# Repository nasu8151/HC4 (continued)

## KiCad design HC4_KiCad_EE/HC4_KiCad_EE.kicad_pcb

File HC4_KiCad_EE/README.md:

Schematics and board of HC4<sub>E</sub> (E means "for Education").

BOM:
[Bill of materials](https://github.com/nasu8151/HC4/blob/main/HC4_KiCad/BOM_HC4.md)

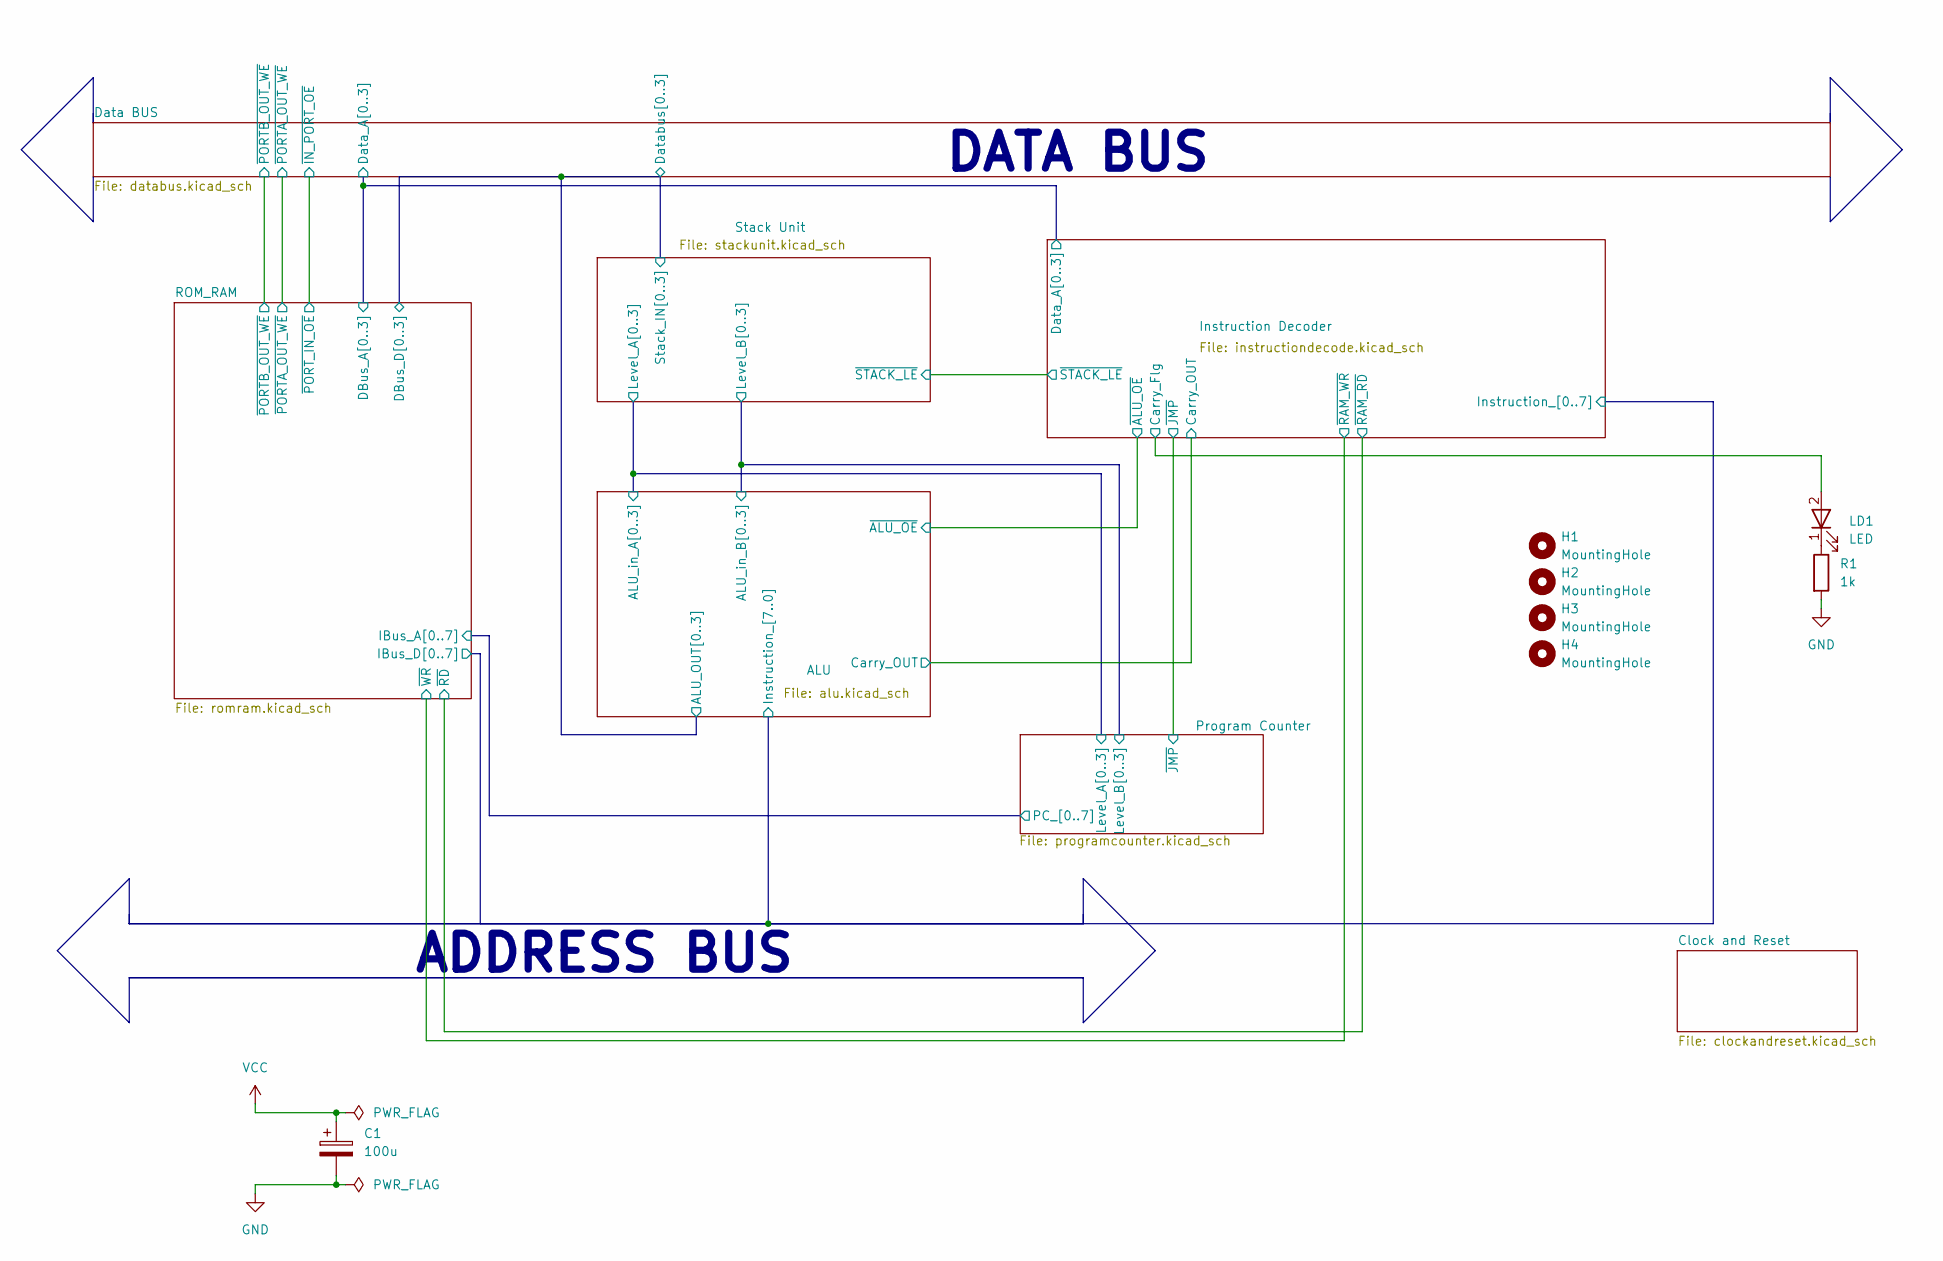
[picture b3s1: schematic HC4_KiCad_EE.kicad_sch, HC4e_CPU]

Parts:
C1: 100u; CP_Radial_D5.0mm_P2.50mm
H1, H2, H3, H4: MountingHole; MountingHole_3.2mm_M3
LD1: LED; LED_Rectangular_W5.0mm_H2.0mm
R1: 1k; R_0603_1608Metric; LCSC PN C21190

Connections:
/Instruction Decoder/Carry_Flg: LD1.2; also elsewhere on the board
GND: C1.2, R1.2; also elsewhere on the board
unnamed: LD1.1 (K_1), R1.1
VCC: C1.1; also elsewhere on the board

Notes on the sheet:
ADDRESS BUS
DATA BUS

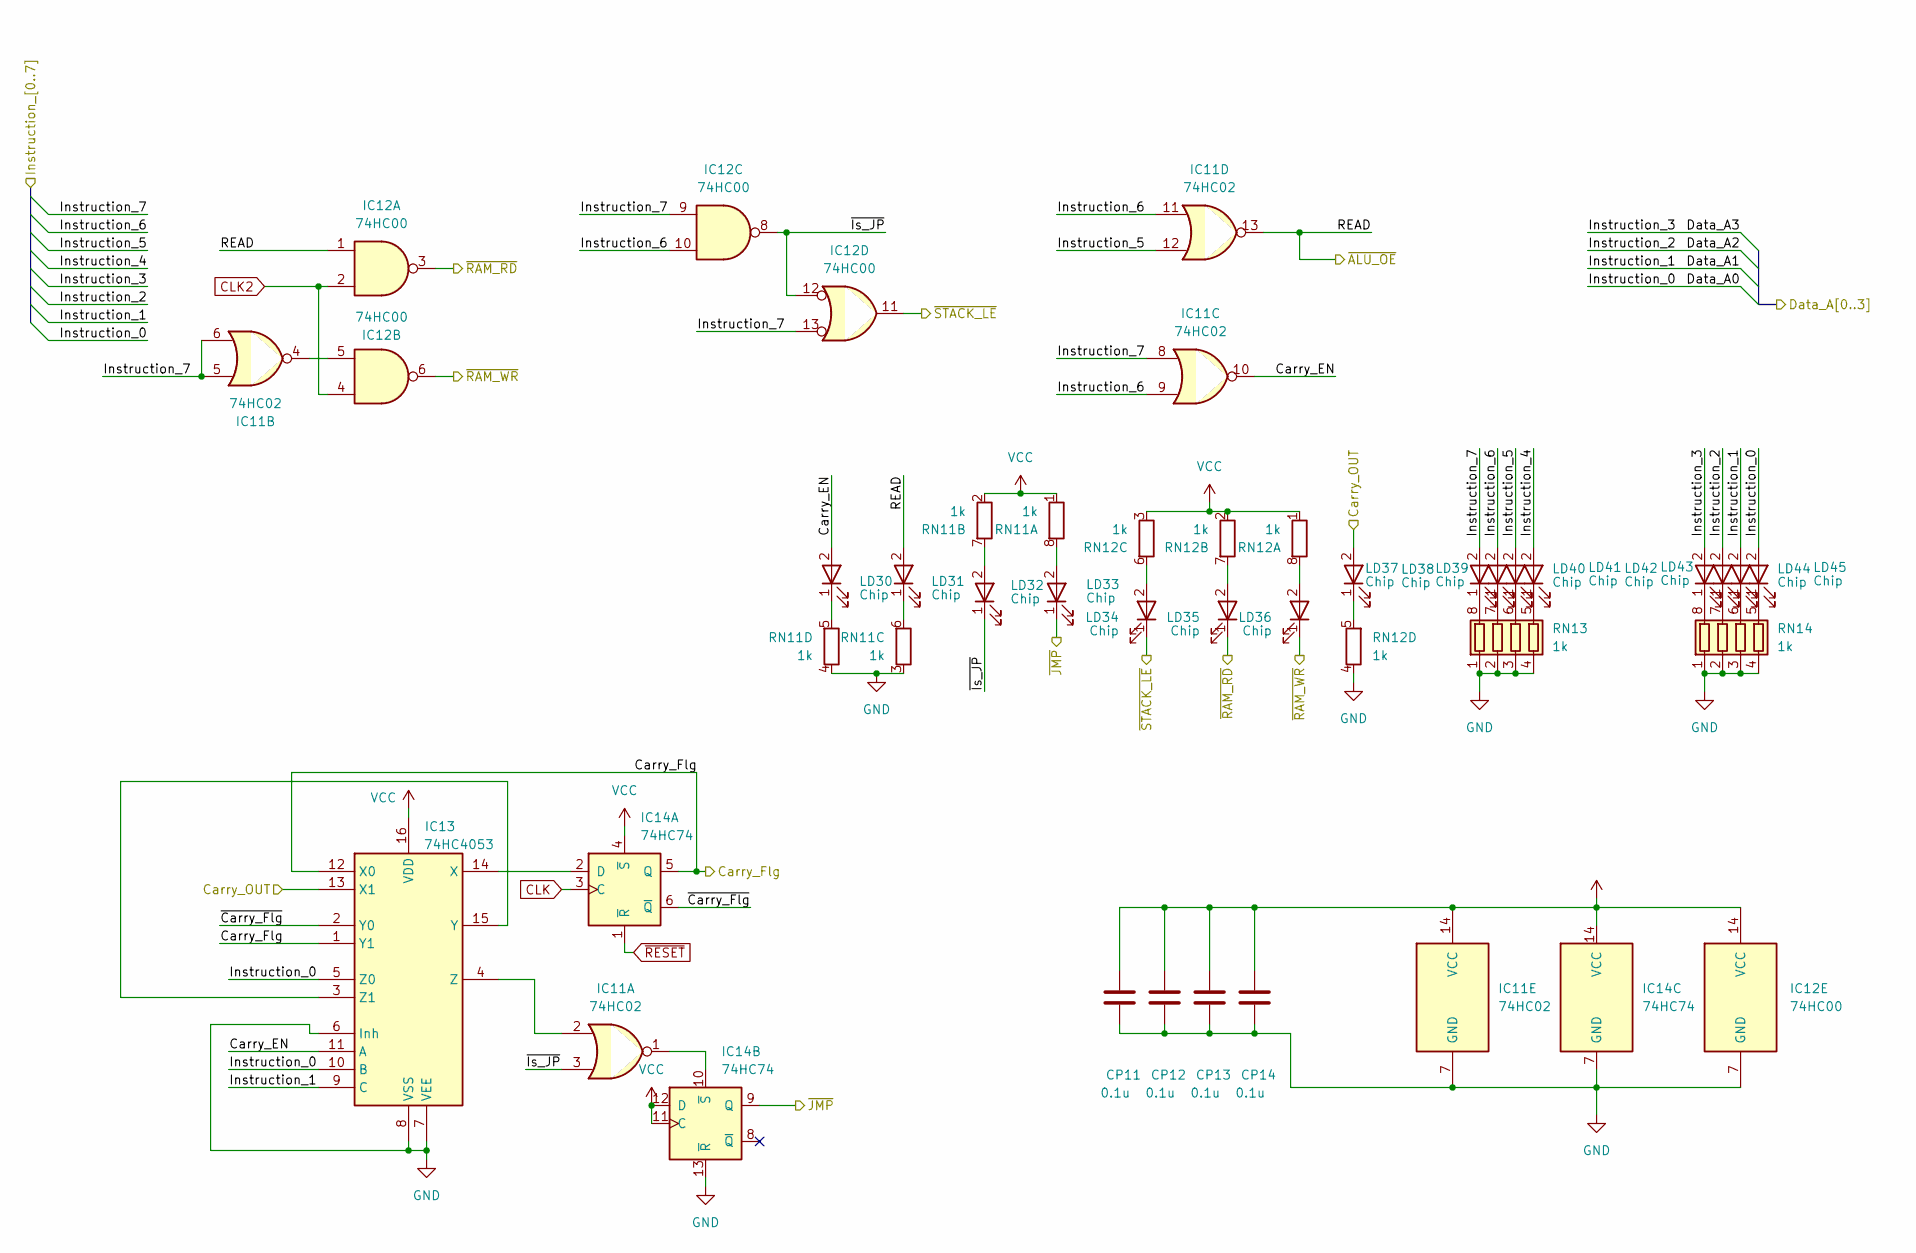
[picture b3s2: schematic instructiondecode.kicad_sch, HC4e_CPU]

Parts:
CP11, CP12, CP13, CP14: 0.1u; C_0603_1608Metric; LCSC PN C14663
IC11: 74HC02; SO-14_5.3x10.2mm_P1.27mm
IC12: 74HC00; SO-14_5.3x10.2mm_P1.27mm
IC13: 74HC4053; SO-16_5.3x10.2mm_P1.27mm
IC14: 74HC74; SO-14_5.3x10.2mm_P1.27mm
LD30, LD31, LD32, LD33, LD34, LD35, LD36, LD37, LD38, LD39, LD40, LD41, LD42, LD43, LD44, LD45: Chip; LED_0603_1608Metric; LCSC PN C2289
RN11, RN12, RN13, RN14: 1k; R_Array_Convex_4x0603; LCSC PN C20197

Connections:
/ALU/Carry_OUT: IC13.13 (X1), LD37.2; also elsewhere on the board
/ALU/Instruction_4: LD41.2; also elsewhere on the board
/ALU/Instruction_5: IC11.12, LD40.2; also elsewhere on the board
/ALU/Instruction_6: IC11.9, IC11.11, IC12.10, LD39.2; also elsewhere on the board
/ALU/Instruction_7: IC11.5, IC11.6, IC11.8, IC12.9, IC12.13, LD38.2; also elsewhere on the board
/Instruction Decoder/Carry_EN: IC11.10, IC13.11 (A), LD30.2
/Instruction Decoder/Carry_Flg: IC13.1 (Y1), IC13.12 (X0), IC14.5 (Q); also elsewhere on the board
/Instruction Decoder/READ: IC11.13, IC12.1, LD31.2; also elsewhere on the board
/Instruction Decoder/~Carry_Flg: IC13.2 (Y0), IC14.6 (~Q)
/Instruction Decoder/~Is_JP: IC11.3, IC12.8, IC12.12, LD32.1 (K_1)
/Instruction Decoder/~JMP: IC14.9 (Q), LD33.1 (K_1); also elsewhere on the board
/Instruction Decoder/~RAM_RD: IC12.3, LD35.1 (K_1); also elsewhere on the board
/Instruction Decoder/~RAM_WR: IC12.6, LD36.1 (K_1); also elsewhere on the board
/Instruction Decoder/~STACK_LE: IC12.11, LD34.1 (K_1); also elsewhere on the board
CLK: IC14.3 (C); also elsewhere on the board
CLK2: IC12.2, IC12.4; also elsewhere on the board
GND: CP11.2, CP12.2, CP13.2, CP14.2, IC11.7 (GND), IC12.7 (GND), IC13.6 (Inh), IC13.7 (VEE), IC13.8 (VSS), IC14.7 (GND), IC14.13 (~R), RN11.3 (R3.1), RN11.4 (R4.1), RN12.4 (R4.1), RN13.1 (R1.1), RN13.2 (R2.1), RN13.3 (R3.1), RN13.4 (R4.1), RN14.1 (R1.1), RN14.2 (R2.1), RN14.3 (R3.1), RN14.4 (R4.1); also elsewhere on the board
unnamed: IC11.4, IC12.5
unnamed: IC13.14 (X), IC14.2 (D)
unnamed: IC13.3 (Z1), IC13.15 (Y)
unnamed: IC11.2, IC13.4 (Z)
unnamed: IC11.1, IC14.10 (~S)
unnamed: LD30.1 (K_1), RN11.5 (R4.2)
unnamed: LD31.1 (K_1), RN11.6 (R3.2)
unnamed: LD37.1 (K_1), RN12.5 (R4.2)
unnamed: LD38.1 (K_1), RN13.8 (R1.2)
unnamed: LD39.1 (K_1), RN13.7 (R2.2)
unnamed: LD40.1 (K_1), RN13.6 (R3.2)
unnamed: LD41.1 (K_1), RN13.5 (R4.2)
unnamed: LD42.1 (K_1), RN14.8 (R1.2)
unnamed: LD43.1 (K_1), RN14.7 (R2.2)
unnamed: LD44.1 (K_1), RN14.6 (R3.2)
unnamed: LD45.1 (K_1), RN14.5 (R4.2)
unnamed: LD33.2, RN11.8 (R1.2)
unnamed: LD32.2, RN11.7 (R2.2)
unnamed: LD36.2, RN12.8 (R1.2)
unnamed: LD35.2, RN12.7 (R2.2)
unnamed: LD34.2, RN12.6 (R3.2)
VCC: CP11.1, CP12.1, CP13.1, CP14.1, IC11.14 (VCC), IC12.14 (VCC), IC13.16 (VDD), IC14.4 (~S), IC14.11 (C), IC14.12 (D), IC14.14 (VCC), RN11.1 (R1.1), RN11.2 (R2.1), RN12.1 (R1.1), RN12.2 (R2.1), RN12.3 (R3.1); also elsewhere on the board
~RESET: IC14.1 (~R); also elsewhere on the board

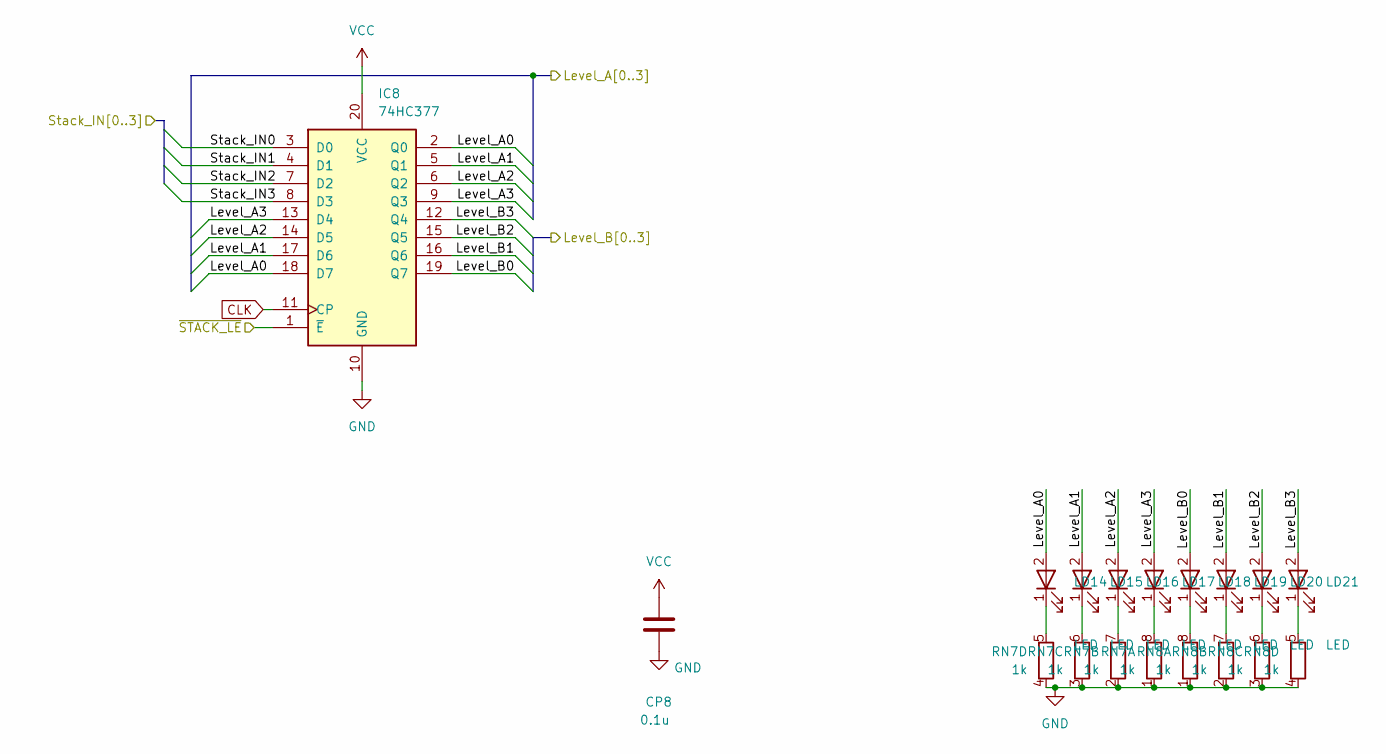
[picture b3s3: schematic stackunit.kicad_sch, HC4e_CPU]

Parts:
CP8: 0.1u; C_0603_1608Metric; LCSC PN C14663
IC8: 74HC377; SOIC-20W_7.5x12.8mm_P1.27mm
LD14, LD15, LD16, LD17, LD18, LD19, LD20, LD21: LED; LED_Rectangular_W5.0mm_H2.0mm
RN7, RN8: 1k; R_Array_Convex_4x0603; LCSC PN C20197

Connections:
/ALU/ALU_OUT0: IC8.3 (D0); also elsewhere on the board
/ALU/ALU_OUT1: IC8.4 (D1); also elsewhere on the board
/ALU/ALU_OUT2: IC8.7 (D2); also elsewhere on the board
/ALU/ALU_OUT3: IC8.8 (D3); also elsewhere on the board
/ALU/ALU_in_A0: IC8.2 (Q0), IC8.18 (D7), LD14.2; also elsewhere on the board
/ALU/ALU_in_A1: IC8.5 (Q1), IC8.17 (D6), LD15.2; also elsewhere on the board
/ALU/ALU_in_A2: IC8.6 (Q2), IC8.14 (D5), LD16.2; also elsewhere on the board
/ALU/ALU_in_A3: IC8.9 (Q3), IC8.13 (D4), LD17.2; also elsewhere on the board
/ALU/ALU_in_B0: IC8.19 (Q7), LD18.2; also elsewhere on the board
/ALU/ALU_in_B1: IC8.16 (Q6), LD19.2; also elsewhere on the board
/ALU/ALU_in_B2: IC8.15 (Q5), LD20.2; also elsewhere on the board
/ALU/ALU_in_B3: IC8.12 (Q4), LD21.2; also elsewhere on the board
/Instruction Decoder/~STACK_LE: IC8.1 (~E); also elsewhere on the board
CLK: IC8.11 (CP); also elsewhere on the board
GND: CP8.2, IC8.10 (GND), RN7.1 (R1.1), RN7.2 (R2.1), RN7.3 (R3.1), RN7.4 (R4.1), RN8.1 (R1.1), RN8.2 (R2.1), RN8.3 (R3.1), RN8.4 (R4.1); also elsewhere on the board
unnamed: LD14.1 (K_1), RN7.5 (R4.2)
unnamed: LD15.1 (K_1), RN7.6 (R3.2)
unnamed: LD16.1 (K_1), RN7.7 (R2.2)
unnamed: LD17.1 (K_1), RN7.8 (R1.2)
unnamed: LD18.1 (K_1), RN8.8 (R1.2)
unnamed: LD19.1 (K_1), RN8.7 (R2.2)
unnamed: LD20.1 (K_1), RN8.6 (R3.2)
unnamed: LD21.1 (K_1), RN8.5 (R4.2)
VCC: CP8.1, IC8.20 (VCC); also elsewhere on the board

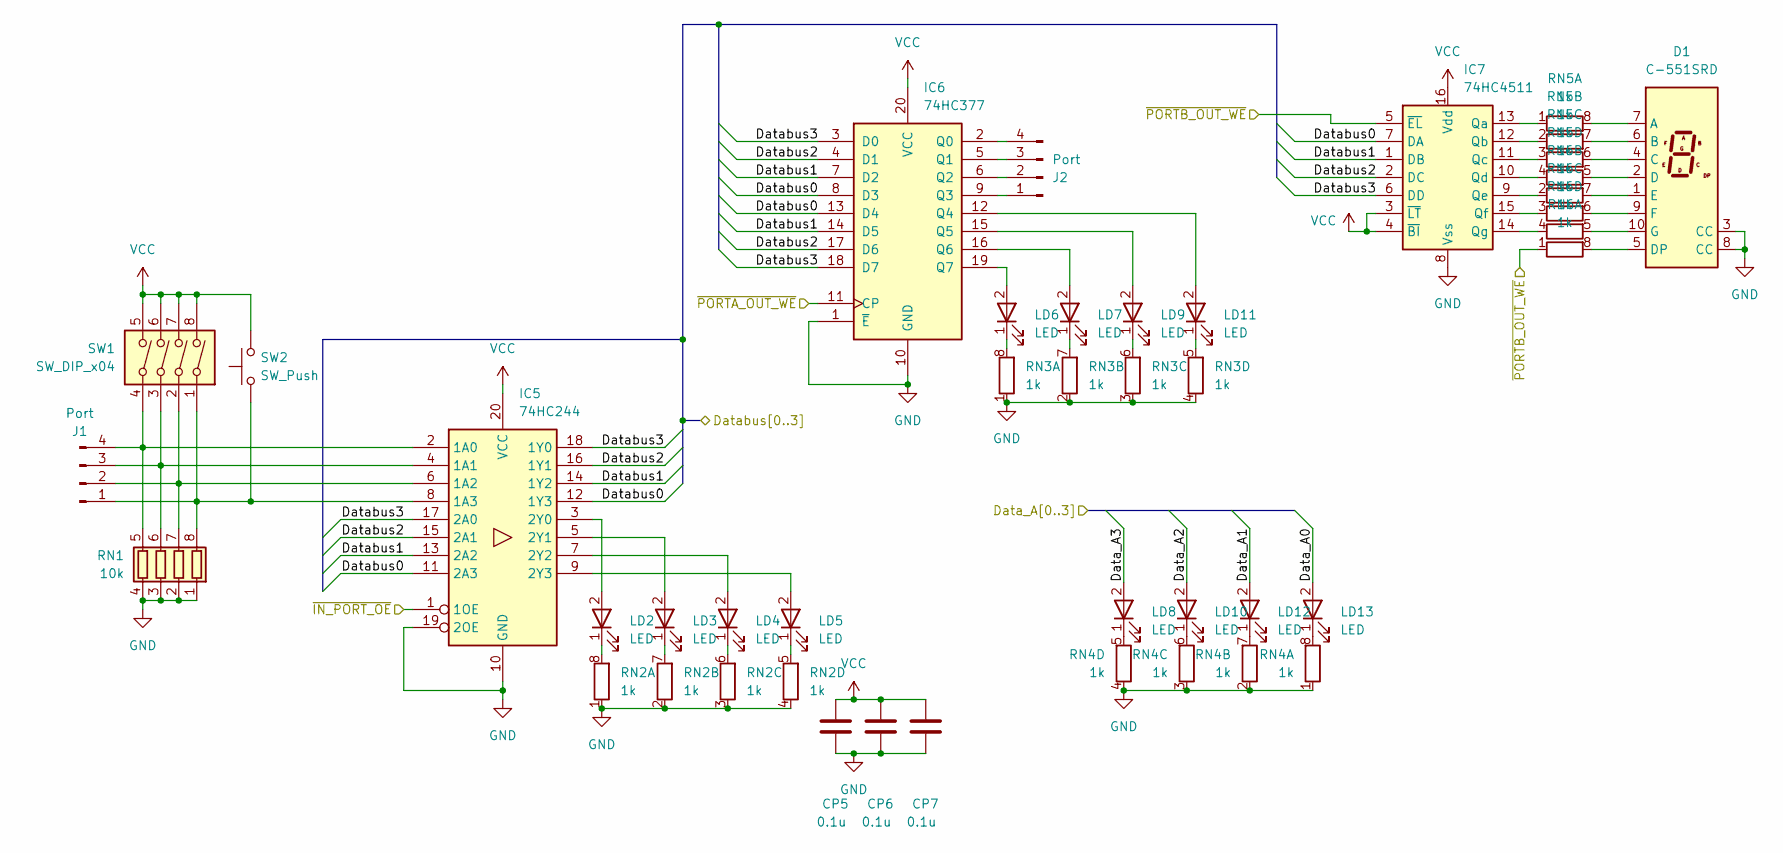
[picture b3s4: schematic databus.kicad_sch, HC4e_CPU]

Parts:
CP5, CP6, CP7: 0.1u; C_0603_1608Metric; LCSC PN C14663
D1: C-551SRD; D1X8K
IC5: 74HC244; SOIC-20W_7.5x12.8mm_P1.27mm
IC6: 74HC377; SOIC-20W_7.5x12.8mm_P1.27mm
IC7: 74HC4511; SO-16_5.3x10.2mm_P1.27mm
J1, J2: Port; PinHeader_1x04_P2.54mm_Vertical
LD2, LD3, LD4, LD5, LD6, LD7, LD8, LD9, LD10, LD11, LD12, LD13: LED; LED_Rectangular_W5.0mm_H2.0mm
RN1: 10k; R_Array_Convex_4x0603; LCSC PN C29718
RN2, RN3, RN4, RN5, RN6: 1k; R_Array_Convex_4x0603; LCSC PN C20197
SW1: SW_DIP_x04; SW_DIP_SPSTx04_Slide_9.78x12.34mm_W7.62mm_P2.54mm
SW2: SW_Push; SW_PUSH_6mm

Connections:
/ALU/ALU_OUT0: IC5.11 (2A3), IC5.12 (1Y3), IC6.8 (D3), IC6.13 (D4), IC7.7 (DA); also elsewhere on the board
/ALU/ALU_OUT1: IC5.13 (2A2), IC5.14 (1Y2), IC6.7 (D2), IC6.14 (D5), IC7.1 (DB); also elsewhere on the board
/ALU/ALU_OUT2: IC5.15 (2A1), IC5.16 (1Y1), IC6.4 (D1), IC6.17 (D6), IC7.2 (DC); also elsewhere on the board
/ALU/ALU_OUT3: IC5.17 (2A0), IC5.18 (1Y0), IC6.3 (D0), IC6.18 (D7), IC7.6 (DD); also elsewhere on the board
/Data BUS/~IN_PORT_OE: IC5.1 (1OE); also elsewhere on the board
/Data BUS/~PORTA_OUT_WE: IC6.11 (CP); also elsewhere on the board
/Data BUS/~PORTB_OUT_WE: IC7.5 (~EL), RN6.1 (R1.1); also elsewhere on the board
GND: CP5.2, CP6.2, CP7.2, D1.3 (CC), D1.8 (CC), IC5.10 (GND), IC5.19 (2OE), IC6.1 (~E), IC6.10 (GND), IC7.8 (Vss), RN1.1 (R1.1), RN1.2 (R2.1), RN1.3 (R3.1), RN1.4 (R4.1), RN2.1 (R1.1), RN2.2 (R2.1), RN2.3 (R3.1), RN2.4 (R4.1), RN3.1 (R1.1), RN3.2 (R2.1), RN3.3 (R3.1), RN3.4 (R4.1), RN4.1 (R1.1), RN4.2 (R2.1), RN4.3 (R3.1), RN4.4 (R4.1); also elsewhere on the board
unnamed: D1.7 (A), RN5.8 (R1.2)
unnamed: D1.6 (B), RN5.7 (R2.2)
unnamed: D1.4 (C), RN5.6 (R3.2)
unnamed: D1.2 (D), RN5.5 (R4.2)
unnamed: D1.5 (DP), RN6.8 (R1.2)
unnamed: D1.1 (E), RN6.7 (R2.2)
unnamed: D1.9 (F), RN6.6 (R3.2)
unnamed: D1.10 (G), RN6.5 (R4.2)
unnamed: IC5.2 (1A0), J1.4, RN1.5 (R4.2), SW1.4
unnamed: IC5.4 (1A1), J1.3, RN1.6 (R3.2), SW1.3
unnamed: IC5.6 (1A2), J1.2, RN1.7 (R2.2), SW1.2
unnamed: IC5.8 (1A3), J1.1, RN1.8 (R1.2), SW1.1, SW2.1
unnamed: IC5.3 (2Y0), LD2.2
unnamed: IC5.5 (2Y1), LD3.2
unnamed: IC5.7 (2Y2), LD4.2
unnamed: IC5.9 (2Y3), LD5.2
unnamed: IC6.2 (Q0), J2.4
unnamed: IC6.5 (Q1), J2.3
unnamed: IC6.6 (Q2), J2.2
unnamed: IC6.9 (Q3), J2.1
unnamed: IC6.12 (Q4), LD11.2
unnamed: IC6.15 (Q5), LD9.2
unnamed: IC6.16 (Q6), LD7.2
unnamed: IC6.19 (Q7), LD6.2
unnamed: IC7.13 (Qa), RN5.1 (R1.1)
unnamed: IC7.12 (Qb), RN5.2 (R2.1)
unnamed: IC7.11 (Qc), RN5.3 (R3.1)
unnamed: IC7.10 (Qd), RN5.4 (R4.1)
unnamed: IC7.9 (Qe), RN6.2 (R2.1)
unnamed: IC7.15 (Qf), RN6.3 (R3.1)
unnamed: IC7.14 (Qg), RN6.4 (R4.1)
unnamed: LD2.1 (K_1), RN2.8 (R1.2)
unnamed: LD3.1 (K_1), RN2.7 (R2.2)
unnamed: LD4.1 (K_1), RN2.6 (R3.2)
unnamed: LD5.1 (K_1), RN2.5 (R4.2)
unnamed: LD6.1 (K_1), RN3.8 (R1.2)
unnamed: LD7.1 (K_1), RN3.7 (R2.2)
unnamed: LD8.1 (K_1), RN4.5 (R4.2)
unnamed: LD9.1 (K_1), RN3.6 (R3.2)
unnamed: LD10.1 (K_1), RN4.6 (R3.2)
unnamed: LD11.1 (K_1), RN3.5 (R4.2)
unnamed: LD12.1 (K_1), RN4.7 (R2.2)
unnamed: LD13.1 (K_1), RN4.8 (R1.2)
VCC: CP5.1, CP6.1, CP7.1, IC5.20 (VCC), IC6.20 (VCC), IC7.3 (~LT), IC7.4 (~BI), IC7.16 (Vdd), SW1.5, SW1.6, SW1.7, SW1.8, SW2.2; also elsewhere on the board

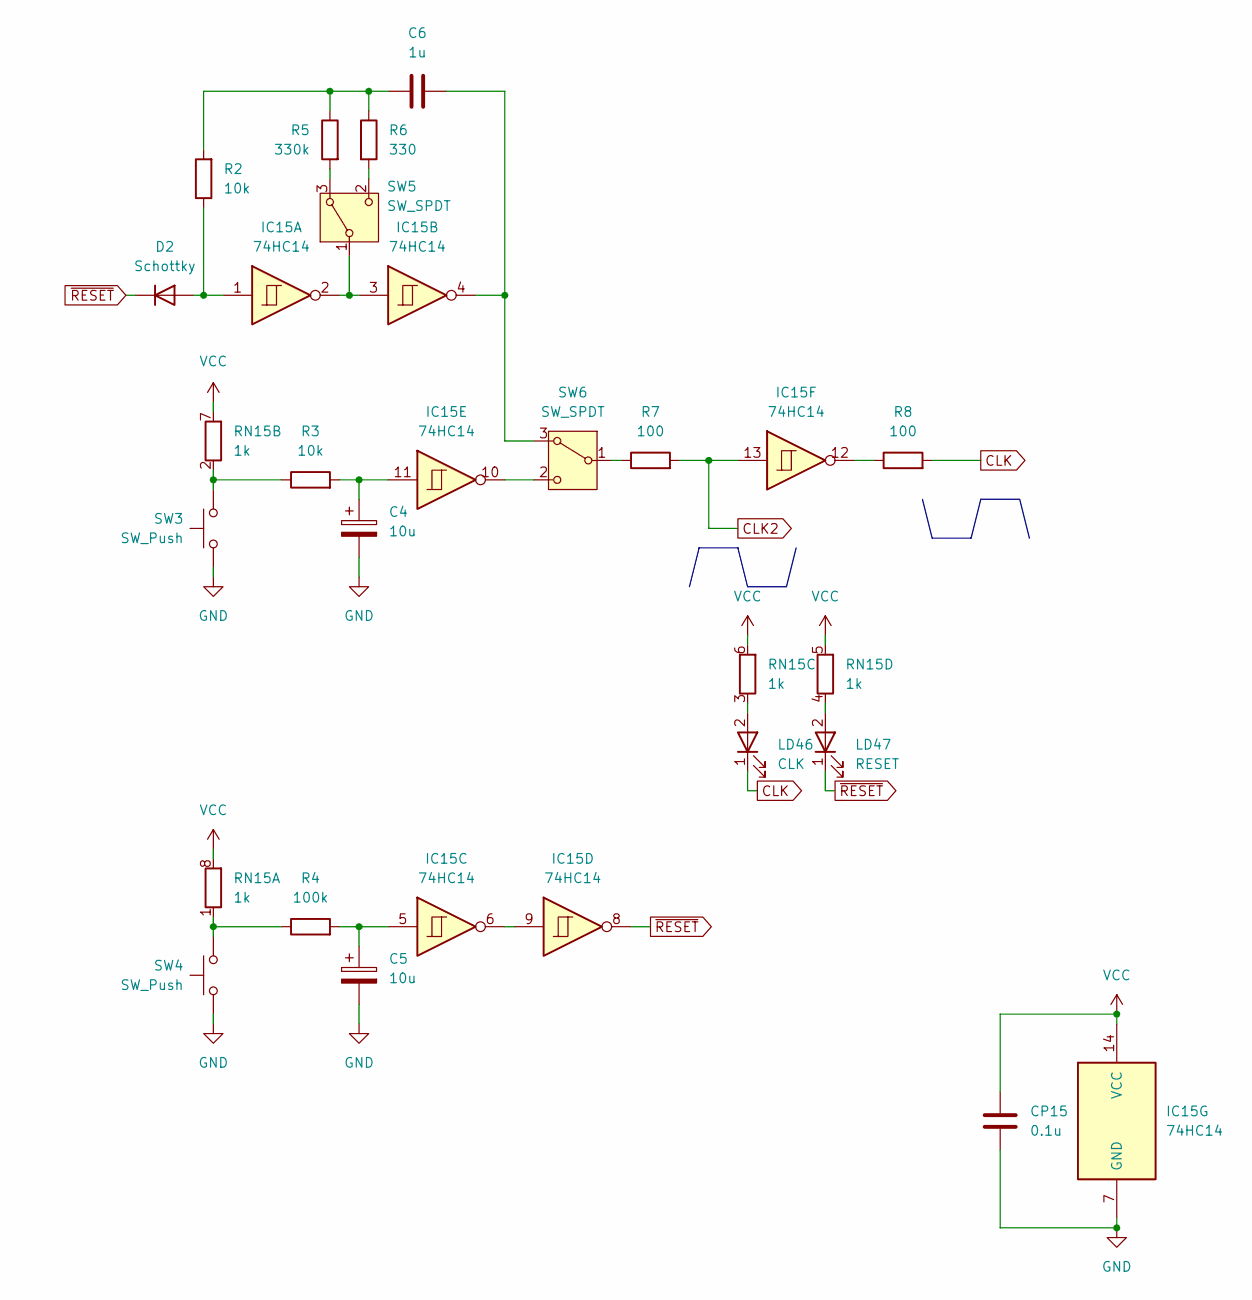
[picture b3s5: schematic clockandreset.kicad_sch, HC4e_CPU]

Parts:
C4, C5: 10u; CP_Radial_D5.0mm_P2.50mm
C6: 1u; C_Radial_D5.0mm_H5.0mm_P2.00mm
CP15: 0.1u; C_0603_1608Metric; LCSC PN C14663
D2: Schottky; D_SOD-323_HandSoldering
IC15: 74HC14; SO-14_5.3x10.2mm_P1.27mm
LD46: CLK; LED_D5.0mm
LD47: RESET; LED_D5.0mm
R2, R3: 10k; R_0603_1608Metric; LCSC PN C25804
R4: 100k; R_0603_1608Metric; LCSC PN C25803
R5: 330k; R_0603_1608Metric; LCSC PN C23137
R6: 330; R_0603_1608Metric; LCSC PN C23151
R7, R8: 100; R_0603_1608Metric; LCSC PN C22775
RN15: 1k; R_Array_Convex_4x0603; LCSC PN C20197
SW3, SW4: SW_Push; SW_PUSH_6mm
SW5, SW6: SW_SPDT; SW_Slide-03_Wuerth-WS-SLTV_10x2.5x6.4_P2.54mm

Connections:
CLK: LD46.1 (K_1), R8.2; also elsewhere on the board
CLK2: IC15.13, R7.2; also elsewhere on the board
GND: C4.2, C5.2, CP15.2, IC15.7 (GND), SW3.1, SW4.1; also elsewhere on the board
unnamed: C4.1, IC15.11, R3.2
unnamed: C5.1, IC15.5, R4.2
unnamed: C6.1, R2.2, R5.1, R6.1
unnamed: D2.2 (A), IC15.1, R2.1
unnamed: IC15.6, IC15.9
unnamed: IC15.12, R8.1
unnamed: R4.1, RN15.1 (R1.1), SW4.2
unnamed: R3.1, RN15.2 (R2.1), SW3.2
unnamed: LD46.2, RN15.3 (R3.1)
unnamed: LD47.2, RN15.4 (R4.1)
unnamed: R5.2, SW5.3 (A)
unnamed: IC15.2, IC15.3, SW5.1 (B)
unnamed: R6.2, SW5.2 (C)
unnamed: C6.2, IC15.4, SW6.3 (A)
unnamed: R7.1, SW6.1 (B)
unnamed: IC15.10, SW6.2 (C)
VCC: CP15.1, IC15.14 (VCC), RN15.5 (R4.2), RN15.6 (R3.2), RN15.7 (R2.2), RN15.8 (R1.2); also elsewhere on the board
~RESET: D2.1 (K), IC15.8, LD47.1 (K_1); also elsewhere on the board

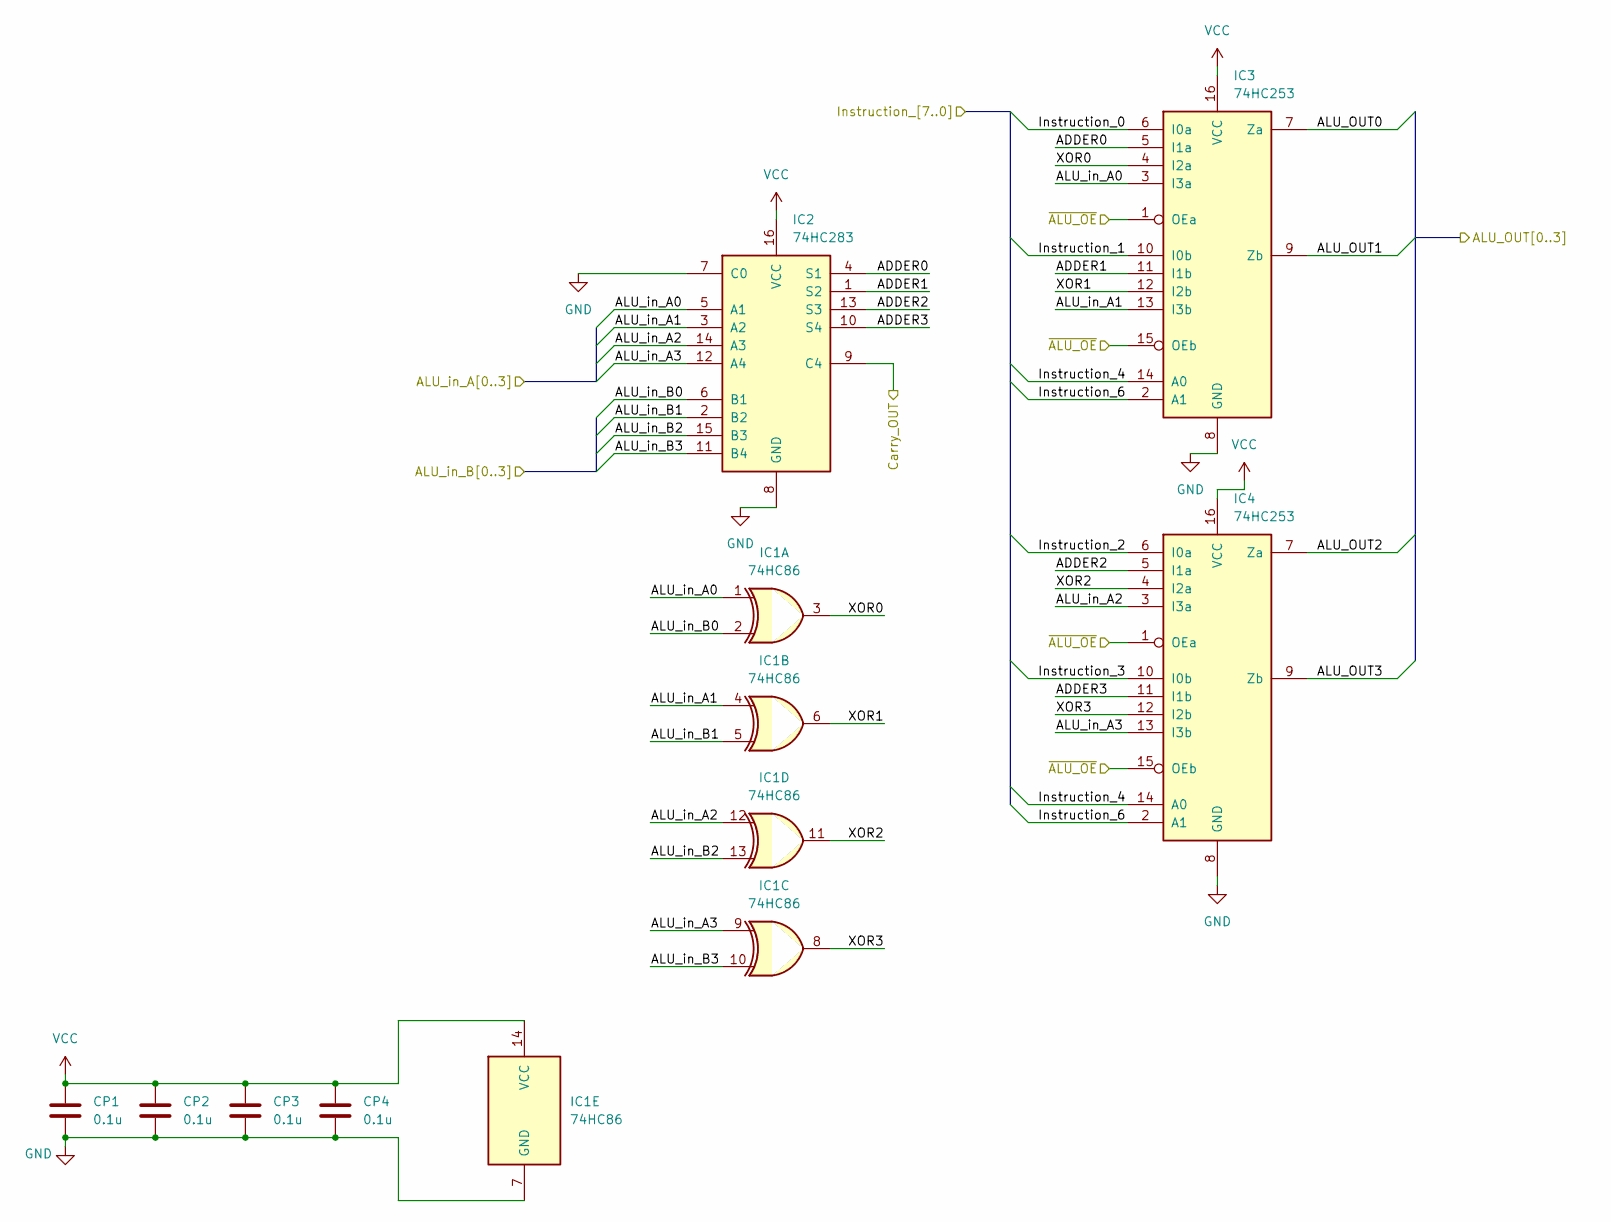
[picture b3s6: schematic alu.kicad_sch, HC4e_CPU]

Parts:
CP1, CP2, CP3, CP4: 0.1u; C_0603_1608Metric; LCSC PN C14663
IC1: 74HC86; SO-14_5.3x10.2mm_P1.27mm
IC2: 74HC283; SO-16_5.3x10.2mm_P1.27mm
IC3, IC4: 74HC253; SO-16_5.3x10.2mm_P1.27mm

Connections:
/ALU/ADDER0: IC2.4 (S1), IC3.5 (I1a)
/ALU/ADDER1: IC2.1 (S2), IC3.11 (I1b)
/ALU/ADDER2: IC2.13 (S3), IC4.5 (I1a)
/ALU/ADDER3: IC2.10 (S4), IC4.11 (I1b)
/ALU/ALU_OUT0: IC3.7 (Za); also elsewhere on the board
/ALU/ALU_OUT1: IC3.9 (Zb); also elsewhere on the board
/ALU/ALU_OUT2: IC4.7 (Za); also elsewhere on the board
/ALU/ALU_OUT3: IC4.9 (Zb); also elsewhere on the board
/ALU/ALU_in_A0: IC1.1, IC2.5 (A1), IC3.3 (I3a); also elsewhere on the board
/ALU/ALU_in_A1: IC1.4, IC2.3 (A2), IC3.13 (I3b); also elsewhere on the board
/ALU/ALU_in_A2: IC1.12, IC2.14 (A3), IC4.3 (I3a); also elsewhere on the board
/ALU/ALU_in_A3: IC1.9, IC2.12 (A4), IC4.13 (I3b); also elsewhere on the board
/ALU/ALU_in_B0: IC1.2, IC2.6 (B1); also elsewhere on the board
/ALU/ALU_in_B1: IC1.5, IC2.2 (B2); also elsewhere on the board
/ALU/ALU_in_B2: IC1.13, IC2.15 (B3); also elsewhere on the board
/ALU/ALU_in_B3: IC1.10, IC2.11 (B4); also elsewhere on the board
/ALU/Carry_OUT: IC2.9 (C4); also elsewhere on the board
/ALU/Instruction_4: IC3.14 (A0), IC4.14 (A0); also elsewhere on the board
/ALU/Instruction_6: IC3.2 (A1), IC4.2 (A1); also elsewhere on the board
/ALU/XOR0: IC1.3, IC3.4 (I2a)
/ALU/XOR1: IC1.6, IC3.12 (I2b)
/ALU/XOR2: IC1.11, IC4.4 (I2a)
/ALU/XOR3: IC1.8, IC4.12 (I2b)
/Instruction Decoder/READ: IC3.1 (OEa), IC3.15 (OEb), IC4.1 (OEa), IC4.15 (OEb); also elsewhere on the board
GND: CP1.2, CP2.2, CP3.2, CP4.2, IC1.7 (GND), IC2.7 (C0), IC2.8 (GND), IC3.8 (GND), IC4.8 (GND); also elsewhere on the board
VCC: CP1.1, CP2.1, CP3.1, CP4.1, IC1.14 (VCC), IC2.16 (VCC), IC3.16 (VCC), IC4.16 (VCC); also elsewhere on the board

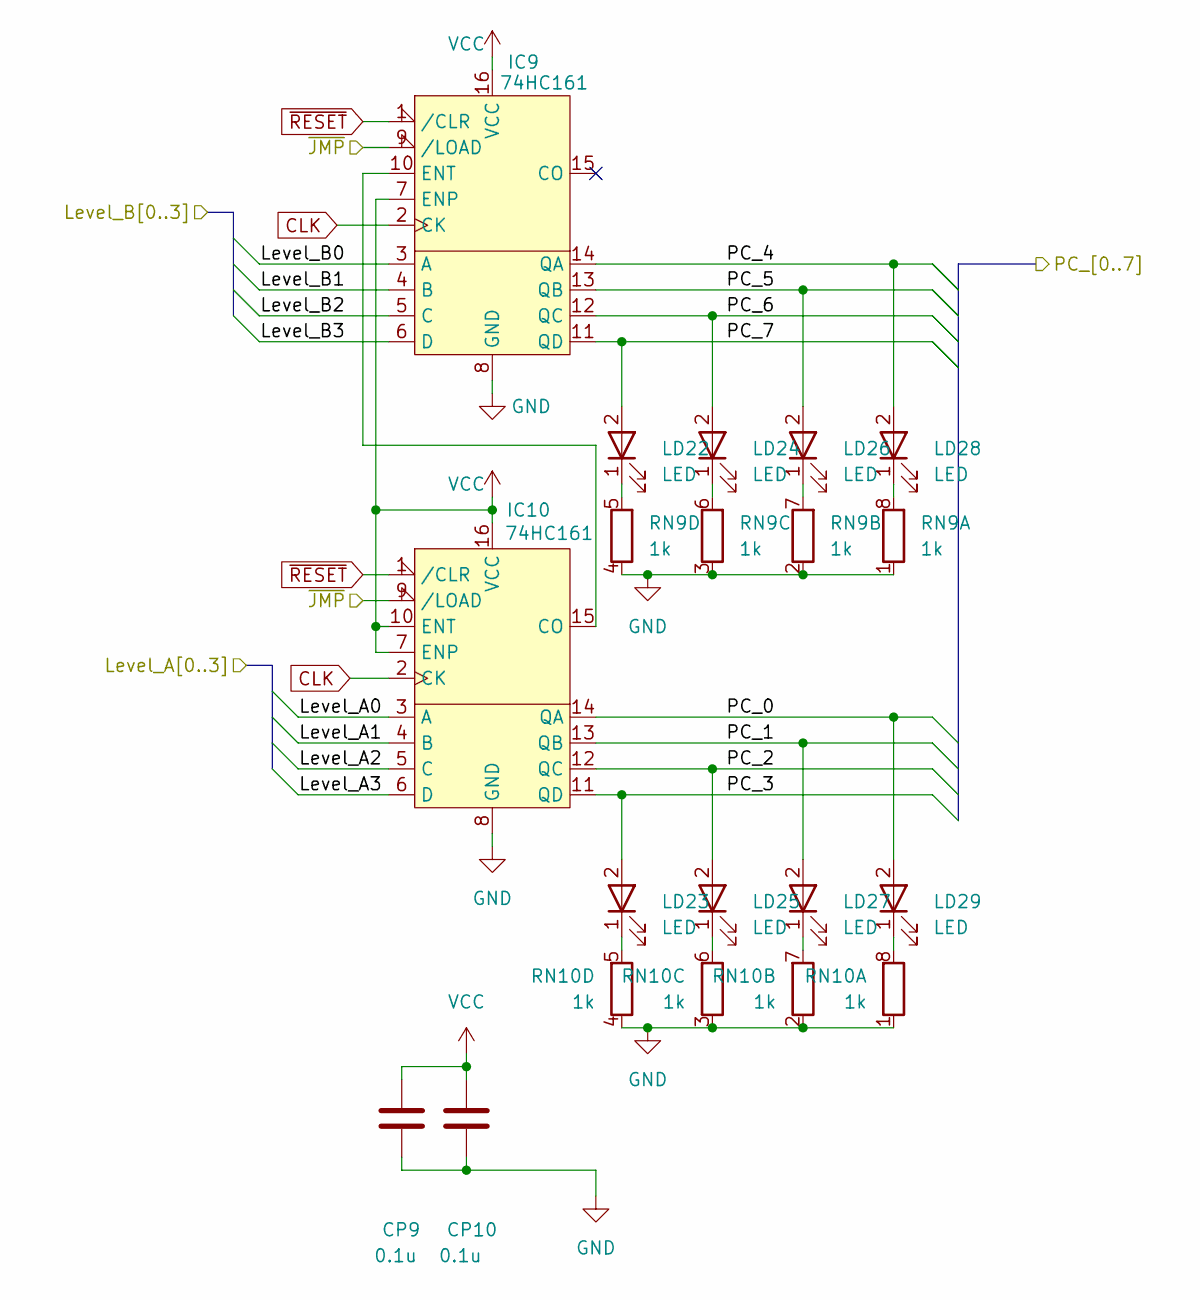
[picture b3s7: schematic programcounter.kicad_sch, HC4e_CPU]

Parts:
CP9, CP10: 0.1u; C_0603_1608Metric; LCSC PN C14663
IC9, IC10: 74HC161; SO-16_5.3x10.2mm_P1.27mm
LD22, LD23, LD24, LD25, LD26, LD27, LD28, LD29: LED; LED_Rectangular_W5.0mm_H2.0mm
RN9, RN10: 1k; R_Array_Convex_4x0603; LCSC PN C20197

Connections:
/ALU/ALU_in_A0: IC10.3 (A); also elsewhere on the board
/ALU/ALU_in_A1: IC10.4 (B); also elsewhere on the board
/ALU/ALU_in_A2: IC10.5 (C); also elsewhere on the board
/ALU/ALU_in_A3: IC10.6 (D); also elsewhere on the board
/ALU/ALU_in_B0: IC9.3 (A); also elsewhere on the board
/ALU/ALU_in_B1: IC9.4 (B); also elsewhere on the board
/ALU/ALU_in_B2: IC9.5 (C); also elsewhere on the board
/ALU/ALU_in_B3: IC9.6 (D); also elsewhere on the board
/Instruction Decoder/~JMP: IC9.9 (/LOAD), IC10.9 (/LOAD); also elsewhere on the board
/Program Counter/PC_0: IC10.14 (QA), LD29.2; also elsewhere on the board
/Program Counter/PC_1: IC10.13 (QB), LD27.2; also elsewhere on the board
/Program Counter/PC_2: IC10.12 (QC), LD25.2; also elsewhere on the board
/Program Counter/PC_3: IC10.11 (QD), LD23.2; also elsewhere on the board
/Program Counter/PC_4: IC9.14 (QA), LD28.2; also elsewhere on the board
/Program Counter/PC_5: IC9.13 (QB), LD26.2; also elsewhere on the board
/Program Counter/PC_6: IC9.12 (QC), LD24.2; also elsewhere on the board
/Program Counter/PC_7: IC9.11 (QD), LD22.2; also elsewhere on the board
CLK: IC9.2 (CK), IC10.2 (CK); also elsewhere on the board
GND: CP9.2, CP10.2, IC9.8 (GND), IC10.8 (GND), RN9.1 (R1.1), RN9.2 (R2.1), RN9.3 (R3.1), RN9.4 (R4.1), RN10.1 (R1.1), RN10.2 (R2.1), RN10.3 (R3.1), RN10.4 (R4.1); also elsewhere on the board
unnamed: IC9.10 (ENT), IC10.15 (CO)
unnamed: LD22.1 (K_1), RN9.5 (R4.2)
unnamed: LD23.1 (K_1), RN10.5 (R4.2)
unnamed: LD24.1 (K_1), RN9.6 (R3.2)
unnamed: LD25.1 (K_1), RN10.6 (R3.2)
unnamed: LD26.1 (K_1), RN9.7 (R2.2)
unnamed: LD27.1 (K_1), RN10.7 (R2.2)
unnamed: LD28.1 (K_1), RN9.8 (R1.2)
unnamed: LD29.1 (K_1), RN10.8 (R1.2)
VCC: CP9.1, CP10.1, IC9.7 (ENP), IC9.16 (VCC), IC10.7 (ENP), IC10.10 (ENT), IC10.16 (VCC); also elsewhere on the board
~RESET: IC9.1 (/CLR), IC10.1 (/CLR); also elsewhere on the board
